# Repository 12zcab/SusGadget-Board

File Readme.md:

## SusGadget

A hack ducky which can maybe do some questionable stuff to your computer or maybe it’s just a sweet little game who knows!
<br>
<br>

## Table of contents
- [Zine page](#Zine)
- [Images](#Images)
- [What is this](#What-is-this)
- [Why I made this](#Why-I-made-this)
- [Parts required](#Parts-required)
- [How to make it yourself](#How-to-make-it-yourself)

<br>
<br>
Huge thanks to Raghav who helped me polish the project and improved many design flaws and zine design :) 

## Zine

## Youtube Demo

[Watch here!](https://youtu.be/1S0NnBTiFww?si=1X6zqkv0NfYqutrI)

## Images

<br>
<br>

## What is this

This is a esp32 S3 supermini based Hackducky, with an OLED display, a joystick and a potentiometer which can be used to execute commands on your friend's computer to prank them or maybe just it as a mini display for timers, temperatures or any other stats, the possibilities are endless! !
it also has a potentiometer and a buzzer so u can may be make some weird beep noise that changes its pitch while u spin the potentiometer and communicate with aliens (welp, who knows?)
Definitely a cool gadget and definitely sus enough :D
<br>
<br>

## Why I made this :|
Humm idk this is like what people think electronic nerds will make : |
(Actually i wanna try to plug in this usb and tell my friend this is just a oled small screen to monitor his computer's temperature then shutdown his computer with Alt+F4+Enter while he plays Roblox :DDDDD)

## Parts required
 1. A 0.91 inch Oled for Display
 2. A Potentiometer for Analog Input
 3. A Joystick Module Connecter
 4. A RGB WS2812 LED on board
 5. A USB-A with CH340 on board serial interface (and for power)
 6. Extend IO Ports (GPIO,I2C)
 7. 5-Way Joy-Stick like Switch
 8. a buzzer :D

## How to make it yourself
 <h3> 1. Acquire parts </h3>
- Navigate to the BOM in the repository and buy the listed parts. <br>
- 3D print the case by acquiring stl files from the 3de print folder in the repository. <br>
- Order PCB by using the gerber files provided in the repository. <br>
 
 <h3> 2. Assembly </h3>
 - Solder all the components on the PCB. <br>
 - Put the soldered PCB in the case. <br>
  
 <h3> 3. Firmware setup </h3>

 - Connect your device to the esp 32 <br>
 - Download the firmware files from the repo <br>
 - Load the firmware <br>

<h3> 4. (most imp step) </h3>
- prank your friends <br>
- have fun  <br>

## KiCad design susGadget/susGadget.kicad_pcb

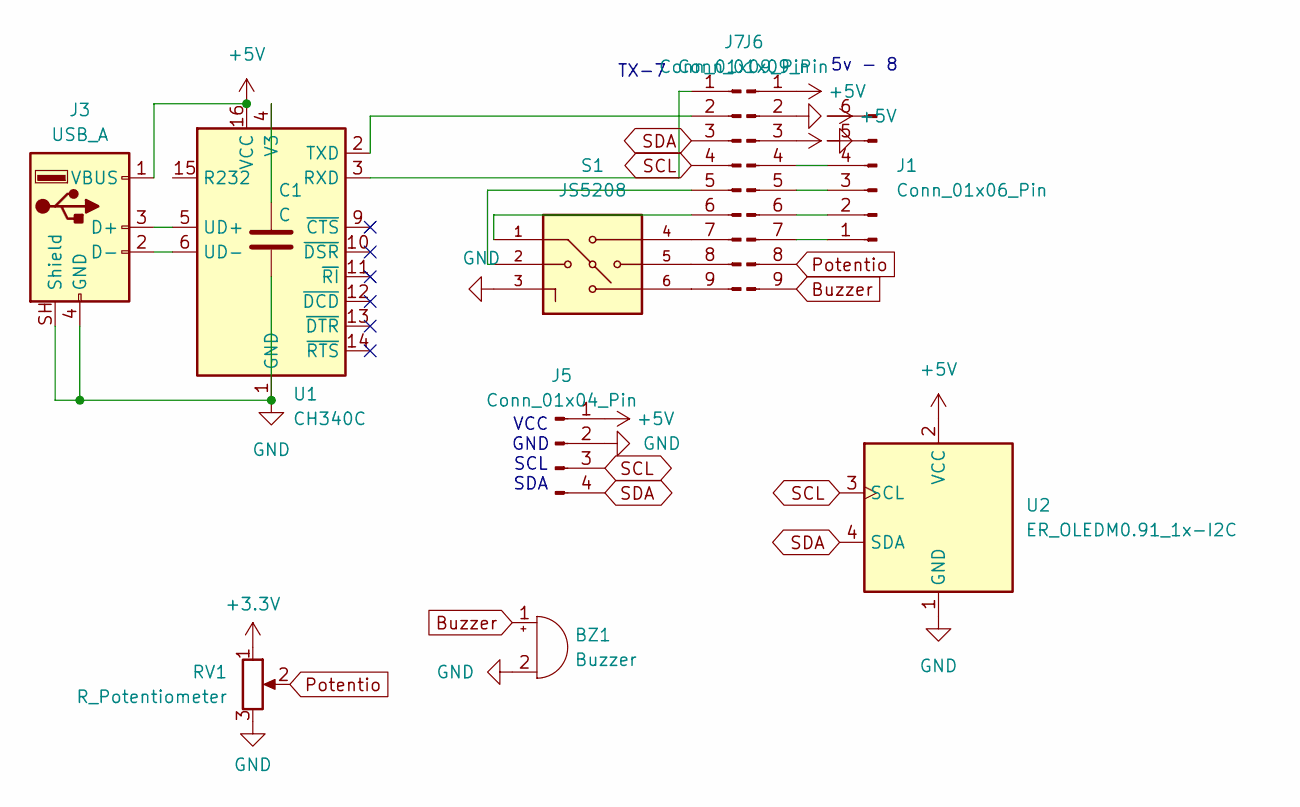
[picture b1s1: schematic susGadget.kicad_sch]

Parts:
BZ1: Buzzer; Buzzer_12x9.5RM7.6
C1: C; C_Disc_D5.0mm_W2.5mm_P2.50mm
J1: Conn_01x06_Pin; PinHeader_1x06_P2.54mm_Horizontal
J3: USB_A; USB_A_Molex_48037-2200_Horizontal
J5: Conn_01x04_Pin; PinHeader_1x04_P2.54mm_Horizontal
J6, J7: Conn_01x09_Pin; PinSocket_1x09_P2.54mm_Vertical
RV1: R_Potentiometer; PinHeader_1x03_P2.54mm_Horizontal
S1: JS5208; SW_JS5208; PARTREV D
U1: CH340C; SOIC-16_3.9x9.9mm_P1.27mm
U2: ER_OLEDM0.91_1x-I2C

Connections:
+3.3V: J6.3, RV1.1
+5V: J1.6, J3.1 (VBUS), J5.1, J6.1, U1.16 (VCC), U2.2 (VCC)
Buzzer: BZ1.1 (+), J6.9
GND: BZ1.2 (-), C1.2, J1.5, J3.4 (GND), J3.SH (Shield), J5.2, J6.2, RV1.3, S1.3, U1.1 (GND), U2.1 (GND)
unnamed: J1.1, J6.7
unnamed: J1.2, J6.6
unnamed: J1.3, J6.5
unnamed: J1.4, J6.4
unnamed: J3.3 (D+), U1.5 (UD+)
unnamed: J3.2 (D-), U1.6 (UD-)
unnamed: J7.1, U1.3 (RXD)
unnamed: J7.2, U1.2 (TXD)
unnamed: J7.5, S1.2
unnamed: J7.6, S1.1
unnamed: J7.7, S1.4
unnamed: J7.8, S1.5
unnamed: J7.9, S1.6
unnamed: C1.1, U1.4 (V3)
Potentio: J6.8, RV1.2
SCL: J5.3, J7.4, U2.3 (SCL)
SDA: J5.4, J7.3, U2.4 (SDA)

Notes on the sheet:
TX-7
5v - 8
VCC GND SCL SDA

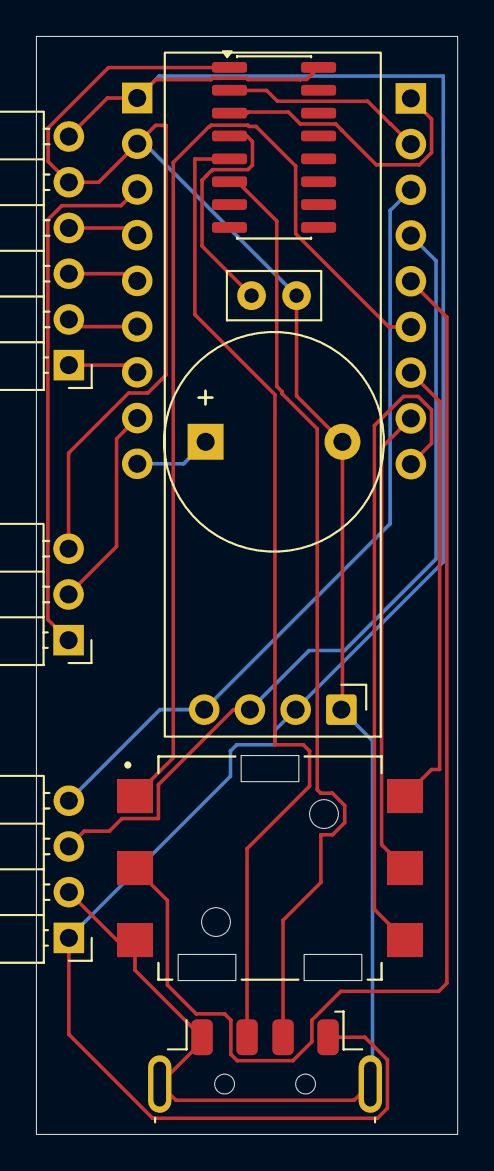
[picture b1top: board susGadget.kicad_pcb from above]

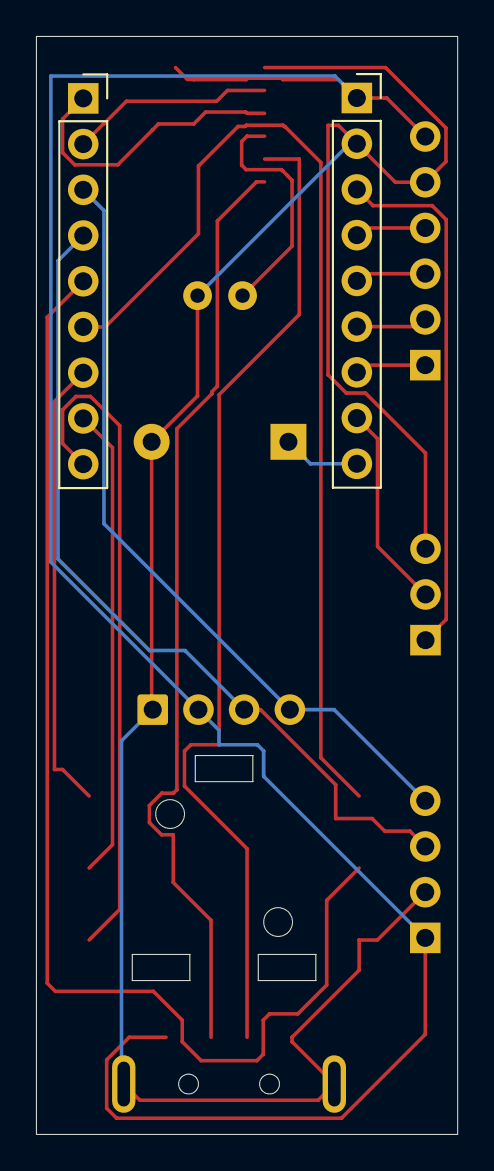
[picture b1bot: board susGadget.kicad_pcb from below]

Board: 2 copper layers, 23.4 x 61.0 mm, 11 parts (2 on the bottom side), 21 nets.
